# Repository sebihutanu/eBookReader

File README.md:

# OpenBook 

## Implementation Steps

### Schematic Design
I used all the required modules (ESP32-C6, BME688, RTC, Display, etc.) based on the reference schematic. I maintained consistent net naming and used components from the provided library.

### Component Placement
I followed the recommended placement, especially for the ESP32 module (antenna area), buttons, USB port, and display header. All components were placed on the TOP layer, as required.

### Manual Routing
Power traces (3V3, VBAT, VBUS, VUSB, VCC, EPD_3V3, EPD_3V3_C) were routed using a width of 0.3 mm, and signal traces were routed with 0.15 mm width.

### Ground Planes & Via Stitching
I created ground planes on both Top and Bottom layers, connected through via stitching. The area under the ESP32 antenna was excluded (no copper or vias) to ensure proper wireless performance.

### Silkscreen & Test Pads
All components were labeled using only their reference designators (R1, C1, etc.) without values. Test pads were clearly labeled in silkscreen (TX, RX, MISO, VBAT, GND, etc.).

### 3D Model & Enclosure
The final 3D model includes the PCB, display, battery (modeled based on datasheet dimensions), and the official provided enclosure. I verified the alignment of the USB port, buttons, and display header with the housing.

## Component List

- **ESP32-C6-WROOM-1-N8**: Main microcontroller. Supports Wi-Fi 6 (2.4GHz), Bluetooth 5, Thread, and Zigbee. Used for control logic and communication. 
    - **Price**: 14.70 RON
    - **Quantity**: 1
    - **Link**: https://ro.mouser.com/datasheet/2/891/Espressif_ESP32_C6_WROOM_1__Datasheet_V0_1_PRELIMI-3239987.pdf
    - **Datasheet**: https://ro.mouser.com/ProductDetail/Espressif-Systems/ESP32-C6-WROOM-1-N8?qs=8Wlm6%252BaMh8ST02Gmwp74cw%3D%3D

- **W25Q512JVEIQ**: 64MB NOR flash memory. Stores firmware, assets, or user data. Communicates via SPI.
    - **Price**: 28.91 RON
    - **Quantity**: 1
    - **Link**: https://ro.mouser.com/ProductDetail/Winbond/W25Q512JVEIQ?qs=l7cgNqFNU1jw6svr3at6tA%3D%3D
    - **Datasheet**: https://ro.mouser.com/datasheet/2/949/Winbond_W25Q512JV_Datasheet-3240039.pdf

- **MAX17048G+T10**: Fuel gauge IC. Provides battery charge level monitoring via I2C.
    - **Price**: 21.19 RON
    - **Quantity**: 1
    - **Link**: https://ro.mouser.com/ProductDetail/Analog-Devices-Maxim-Integrated/MAX17048G%2bT10?qs=D7PJwyCwLAoGnnn8jEPRBQ%3D%3D
    - **Datasheet**: https://ro.mouser.com/datasheet/2/609/MAX17048_MAX17049-3469099.pdf

- **MCP73831**: Li-Ion/Li-Poly battery charging IC. Controls charging current and status indication.
    - **Price**: 3.72 RON
    - **Quantity**: 1
    - **Link**: https://ro.mouser.com/ProductDetail/Microchip-Technology/MCP73831-2ACI-MC?qs=hH%252BOa0VZEiBneYTVdpuVdg%3D%3D
    - **Datasheet**: https://ro.mouser.com/datasheet/2/268/MCP73831_Family_Data_Sheet_DS20001984H-3441711.pdf

- **XC6220A331MR-G**: Low-dropout (LDO) voltage regulator. Converts USB input (5V) to stable 3.3V for the system.
    - **Price**: 2.50 RON
    - **Quantity**: 1
    - **Link**: https://ro.mouser.com/ProductDetail/Torex-Semiconductor/XC6220A331MR-G?qs=AsjdqWjXhJ8ZSWznL1J0gg%3D%3D
    - **Datasheet**: https://ro.mouser.com/datasheet/2/760/xc6220-3371556.pdf

- **DS3231SN#**: High-accuracy real-time clock (RTC) with battery backup. Communicates over I2C.
    - **Price**: 7.23 RON
    - **Quantity**: 1
    - **Link**: https://ro.mouser.com/ProductDetail/Maxim-Integrated/DS3231SN%23?qs=0x2j%252B5q%252B3v4%252B7g%252B6J9wXQ%3D%3D
    - **Datasheet**: https://ro.mouser.com/datasheet/2/609/DS3231-DS3231M-DS3231S

- **BME688 (ESP32_WROVER_BME688)**: Environmental sensor. Measures temperature, humidity, pressure, and gas (VOC). Uses I2C.
    - **Price**: 48.90 RON
    - **Quantity**: 1
    - **Link**: https://ro.mouser.com/ProductDetail/Bosch-Sensortec/BME688?qs=IS%252B4QmGtzzqQoVDscqwx3A%3D%3D
    - **Datasheet**: https://ro.mouser.com/datasheet/2/783/bst_bme688_fl000-2307034.pdf

- **CPH3225A**: Supercapacitor used for RTC backup power.
    - **Price**: 11.04 RON
    - **Quantity**: 1
    - **Link**: https://ro.mouser.com/ProductDetail/Seiko-Semiconductors/CPH3225A?qs=3etwrb1wR%252BhUOph6lAO7eg%3D%3D
    - **Datasheet**: https://ro.mouser.com/datasheet/2/360/Seiko_Instruments_MicroBattery_E_20230330_2024Jan_-3561061.pdf

- **744043680IND_4828-WE-TPC_WRE**: Inductor (68µH). Used for filtering or part of the power supply circuit.
    - **Price**: 6.44 RON
    - **Quantity**: 1
    - **Link**: https://ro.mouser.com/ProductDetail/Wurth-Elektronik/744043680?qs=PGXP4M47uW6VkZq%252BkzjrHA%3D%3D
    - **Datasheet**: https://www.we-online.com/components/products/datasheet/744043680.pdf

- **MBR0530**: Schottky diodes. Used for reverse voltage protection and power path steering.
    - **Price**: 0.90 RON
    - **Quantity**: 3
    - **Link**: https://ro.mouser.com/ProductDetail/onsemi/MBR0530T3G?qs=3JMERSakebpEmdUS6GetdQ%3D%3D
    - **Datasheet**: https://www.onsemi.com/PowerSolutions/product.do?id=MBR0530T3G

- **BD5229G-TR**: Voltage detector. Used for power-on reset or system supervisory functions.
    - **Price**: 3.72 RON
    - **Quantity**: 1
    - **Link**: https://ro.mouser.com/ProductDetail/ROHM-Semiconductor/BD5229G-TR?qs=4kLU8WoGk0vvnhrrYwdszw%3D%3D
    - **Datasheet**: https://fscdn.rohm.com/en/products/databook/datasheet/ic/power/voltage_detector/bd52xxg-e.pdf

- **SI1308EDL-T1-GE3**: N-channel MOSFET. Used for switching or power control.
    - **Price**: 2.07 RON
    - **Quantity**: 1
    - **Link**: https://ro.mouser.com/ProductDetail/Vishay-Semiconductors/SI1308EDL-T1-GE3?qs=bX1%252BNvsK%2FBramh9tgpOaEw%3D%3D
    - **Datasheet**: https://www.vishay.com/doc?63399

- **DMG2305UX**: P-channel MOSFET. Used in power switching or display driving.
    - **Price**: 0.95 RON
    - **Quantity**: 2
    - **Link**: https://ro.mouser.com/ProductDetail/Diodes-Incorporated/DMG2305UX-7?qs=L1DZKBg7t5F%2FNBHrjfxC%252Bg%3D%3D
    - **Datasheet**: https://www.diodes.com/assets/Datasheets/DMG2305UX.pdf

- **USBLC6-2SC6Y**: ESD protection array for USB lines.
    - **Price**: 2.16 RON
    - **Quantity**: 1
    - **Link**: https://ro.mouser.com/ProductDetail/STMicroelectronics/USBLC6-2SC6Y?qs=gNDSiZmRJS%2FOgDexvXkdow%3D%3D
    - **Datasheet**: https://ro.mouser.com/datasheet/2/389/usblc6_2sc6y-1852505.pdf

- **PGB1010603MR**: ESD suppressor / protection component for various I/O lines.
    - **Price**: 1.98 RON
    - **Quantity**: 6
    - **Link**: https://ro.mouser.com/ProductDetail/Littelfuse/PGB1010603MR?qs=gu7KAQ731URLg4GSnNNN7Q%3D%3D
    - **Datasheet**: https://www.littelfuse.com/assetdocs/pulseguard-esd-suppressors-pgb1-datasheet?assetguid=8a337998-d54d-466b-be4e-dc5bcd1f9321

- **TPTP20R**: Test pads. Used for debugging and electrical measurements (e.g. TX, RX, GND, etc.).

- **FH34SRJ-24S-0.5SH(99)**: FPC connector. Used for connecting the e-paper display.
    - **Price**: 12.87 RON
    - **Quantity**: 1
    - **Link**: https://ro.mouser.com/ProductDetail/Hirose-Connector/FH34SRJ-24S-0.5SH99?qs=vcbW%252B4%252BSTIpKBl5ap9J8Fw%3D%3D
    - **Datasheet**: https://ro.mouser.com/datasheet/2/185/FH34SRJ_24S_0_5SH_99__CL0580_1255_6_99_2DDrawing_0-1615044.pdf

- **SAMACSYS_PARTS_USB4110-GF-A**: USB Type-C connector. Used for charging and potential data communication.
    - **Price**: 5.84 RON
    - **Quantity**: 1
    - **Link**: https://ro.mouser.com/ProductDetail/GCT/USB4110-GF-A?qs=KUoIvG%2F9IlYiZvIXQjyJeA%3D%3D
    - **Datasheet**: https://ro.mouser.com/datasheet/2/837/GCT_USB4110_Product_Drawing___20k_cycles-3455479.pdf

- **112A-TAAR-R03_ATTEND3DMODEL**: MicroSD card connector (Push-Push type).
    - **Price**: 7.08 RON
    - **Quantity**: 1
    - **Link**: https://www.digikey.in/en/products/detail/attend-technology/112A-TAAR-R03/17633923
    - **Datasheet**: https://www.attend.com.tw/data/download/file/112A-TAAR-R03_Spec.pdf

- **QWIIC_CONNECTORJS-1MM**: Qwiic I2C connector. Simplifies connecting I2C peripherals.
    - **Price**: 2.30 RON
    - **Quantity**: 1
    - **Link**: https://www.sparkfun.com/qwiic-jst-connector-smd-4-pin-horizontal.html
    - **Datasheet**: https://cdn.sparkfun.com/assets/parts/1/2/2/8/9/Qwiic_Connector_Datasheet.pdf

- **BUTTON_CUSYOMV1**: Push buttons for user input. Includes RESET, BOOT, and FUNCTION buttons.

- **SJ**: Solder jumper. Used to configure hardware options or break/join signals manually.
    - **Price**: 0.55 RON
    - **Quantity**: 1
    - **Link**: https://ro.mouser.com/ProductDetail/Walsin/WR08X000-PGL?qs=1mbolxNpo8eMafhL38cnrw%3D%3D
    - **Datasheet**: https://www.farnell.com/datasheets/2813407.pdf

- **ESP32C6_VARISTORCN1812**: Varistor. Protects against voltage spikes on power lines.
    - **Price**: 2.68 RON
    - **Quantity**: 1
    - **Link**: https://ro.mouser.com/ProductDetail/Bourns/MOV-14D101K?qs=CQ3B1E%252BbPs1zZItCYuJaag%3D%3D
    - **Datasheet**: https://www.mouser.com/datasheet/2/54/MOV14D-57555.pdf?srsltid=AfmBOor_t5WSKE0HqggGW0q-lqbsQwPTZJZ8SAvWUZSrGmLf1ZZCwM8q

- **ESP32_WROVER_AVX (SD0805S020S1R0)**: Schottky diode (another variant). Also used for power line protection.
    - **Price**: 1.46 RON
    - **Quantity**: 1
    - **Link**: https://ro.mouser.com/ProductDetail/KYOCERA-AVX/SD0805S020S1R0?qs=jCA%252BPfw4LHbpkAoSnwrdjw%3D%3D
    - **Datasheet**: https://ro.mouser.com/datasheet/2/40/schottky-3165252.pdf

- **ADAFRUIT_LEDCHIP-LED0603**: Surface-mount LED (0603). Used as charge indicator or status LED.
    - **Price**: 0.50 RON
    - **Quantity**: 1
    - **Link**: https://www.niden.ro/led-uri-smd/4560-led-smd-0603-alb-rece.html
    - **Datasheet**: https://www.mouser.com/datasheet/2/423/LSM0603472V_(1)-1379786.pdf?srsltid=AfmBOoqr62HLQ-IfSohXT73tjl0UQHGyLpv_UpJG0VLORMsRNFTPFgMo

- **EAGLE-LTSPICE_CC0402 / RR0402 / RCL_CPOL-EUCT3528**: Capacitors and resistors in SMD packages. Used for decoupling, filtering, and biasing.
    - **Price**: 0.10 RON
    - **Quantity**: 1
    - **Link**: https://www.digikey.com/en/products/detail/rohm-semiconductor/CC0402/1000000
    - **Datasheet**: https://www.rohm.com/datasheet/CC0402

- **CC0402**: Capacitor (0402 package). Used for decoupling and filtering.
    - **Price**: 0.52 RON
    - **Quantity**: 24
    - **Link**: https://ro.mouser.com/ProductDetail/TAIYO-YUDEN/MCASU105SCG100JFNA01?qs=HFfMDpzxxd3IzDXquDJtfA%3D%3D
    - **Datasheet**: https://ro.mouser.com/datasheet/2/396/TAIYO_YUDEN_04_29_2024_MCASU105SCG100JFNA01_SS-3451431.pdf

- **RR0402**: Resistor (0402 package). Used for pull-up/pull-down or biasing.
    - **Price**: 0.27 RON
    - **Quantity**: 24
    - **Link**: https://ro.mouser.com/ProductDetail/Vishay-Dale/CRCW04020000Z0EEHP?qs=Imq1NPwxi74NTc567q7flQ%3D%3D
    - **Datasheet**: https://www.vishay.com/doc?20043

- **RCL_CPOL-EUCT3528**: Capacitor (EUCT3528 package). Used for decoupling and filtering.
    - **Price**: 6.50 RON
    - **Quantity**: 1
    - **Link**: https://ro.mouser.com/ProductDetail/Vishay-Sprague/TX3B336K016C1000?qs=HFfMDpzxxd327XT3TleiYg%3D%3D
    - **Datasheet**: https://www.vishay.com/doc?40283

- **Battery**: 3.7V Li-Ion battery (not included in the schematic). Used for powering the device when not connected to USB.
    - **Price**: 29.50 RON
    - **Quantity**: 1
    - **Link**: https://www.tme.eu/Document/e0683d8c34e6d878124489f71bffb6ee/cel0014.pdf
    - **Datasheet**: https://www.tme.eu/Document/e0683d8c34e6d878124489f71bffb6ee/cel0014.pdf

- **Display**: E-paper display (not included in the schematic). Used for displaying information to the user.
    - **Price**: 258.85 RON
    - **Quantity**: 1
    - **Link**: https://www.waveshare.com/7.5inch-e-paper-hat.htm
    - **Datasheet**: https://files.waveshare.com/upload/6/60/7.5inch_e-Paper_V2_Specification.pdf
    
> **Total Cost**: 485.50 RON (approx. 100 EUR)

> **Note:** All standard resistors and capacitors are SMD 0402 unless otherwise specified. Decoupling capacitors (100nF) are placed close to IC power pins for stability.

## Block Diagram

## ESP32-C6 Pin Utilization

| ESP32-C6 Pin | Signal Name   | Connected Component         | Description / Purpose                                           |
|--------------|---------------|-----------------------------|-----------------------------------------------------------------|
| EN           | RESET         | -                           | Reset input, active HIGH; used to restart the microcontroller   |
| GPIO0        | INT_RTC       | RTC (DS3231)                | External interrupt input from RTC alarm                         |
| GPIO1        | 32KHZ         | RTC (DS3231)                | 32 kHz reference clock from RTC                                 |
| GPIO2        | MISO          | SD card / Flash             | SPI MISO line for data input                                    |
| GPIO3        | EPD_BUSY      | E-paper display             | Busy status from EPD module                                     |
| GPIO4        | SS_SD         | SD card                     | Chip select for SD card on SPI                                  |
| GPIO5        | EPD_DC        | E-paper display             | Data/command control signal for EPD                             |
| GPIO6        | SCK           | SPI bus                     | Serial clock for SPI communication                              |
| GPIO7        | MOSI          | SPI bus                     | SPI data output                                                 |
| GPIO8        | GPIO8         | -                           | Unused general-purpose pin (test/debug)                         |
| GPIO9        | IO/BOOT       | Push-button                 | Used to enter bootloader mode for programming                   |
| GPIO10       | EPD_CS        | E-paper display             | Chip select for EPD module                                      |
| GPIO11       | FLASH_CS      | External flash (W25Q512)    | Chip select for SPI flash memory                                |
| GPIO12       | USB_D-        | USB-C connector             | USB differential data line (negative)                           |
| GPIO13       | USB_D+        | USB-C connector             | USB differential data line (positive)                           |
| GPIO15       | IO/CHANGE     | Push-button                 | General-purpose button input                                    |
| GPIO16 (TXD) | TX            | UART                        | Serial transmission line                                        |
| GPIO17 (RXD) | RX            | UART                        | Serial reception line                                           |
| GPIO18       | RTC_RST       | RTC (DS3231)                | Reset control for RTC                                           |
| GPIO19       | I2C_RST       | I2C devices                 | I2C reset or control signal                                     |
| GPIO20       | EPD_3V3_C     | E-paper display             | Power control or monitoring line for EPD                        |
| GPIO21       | SDA           | I2C devices (BME688, Fuel Gauge) | I2C data line for sensors and peripherals                  |
| GPIO22       | SCL           | I2C devices (BME688, Fuel Gauge) | I2C clock line for sensors and peripherals                 |
| GPIO23       | EPD_RST       | E-paper display             | Reset signal for the EPD display                                |

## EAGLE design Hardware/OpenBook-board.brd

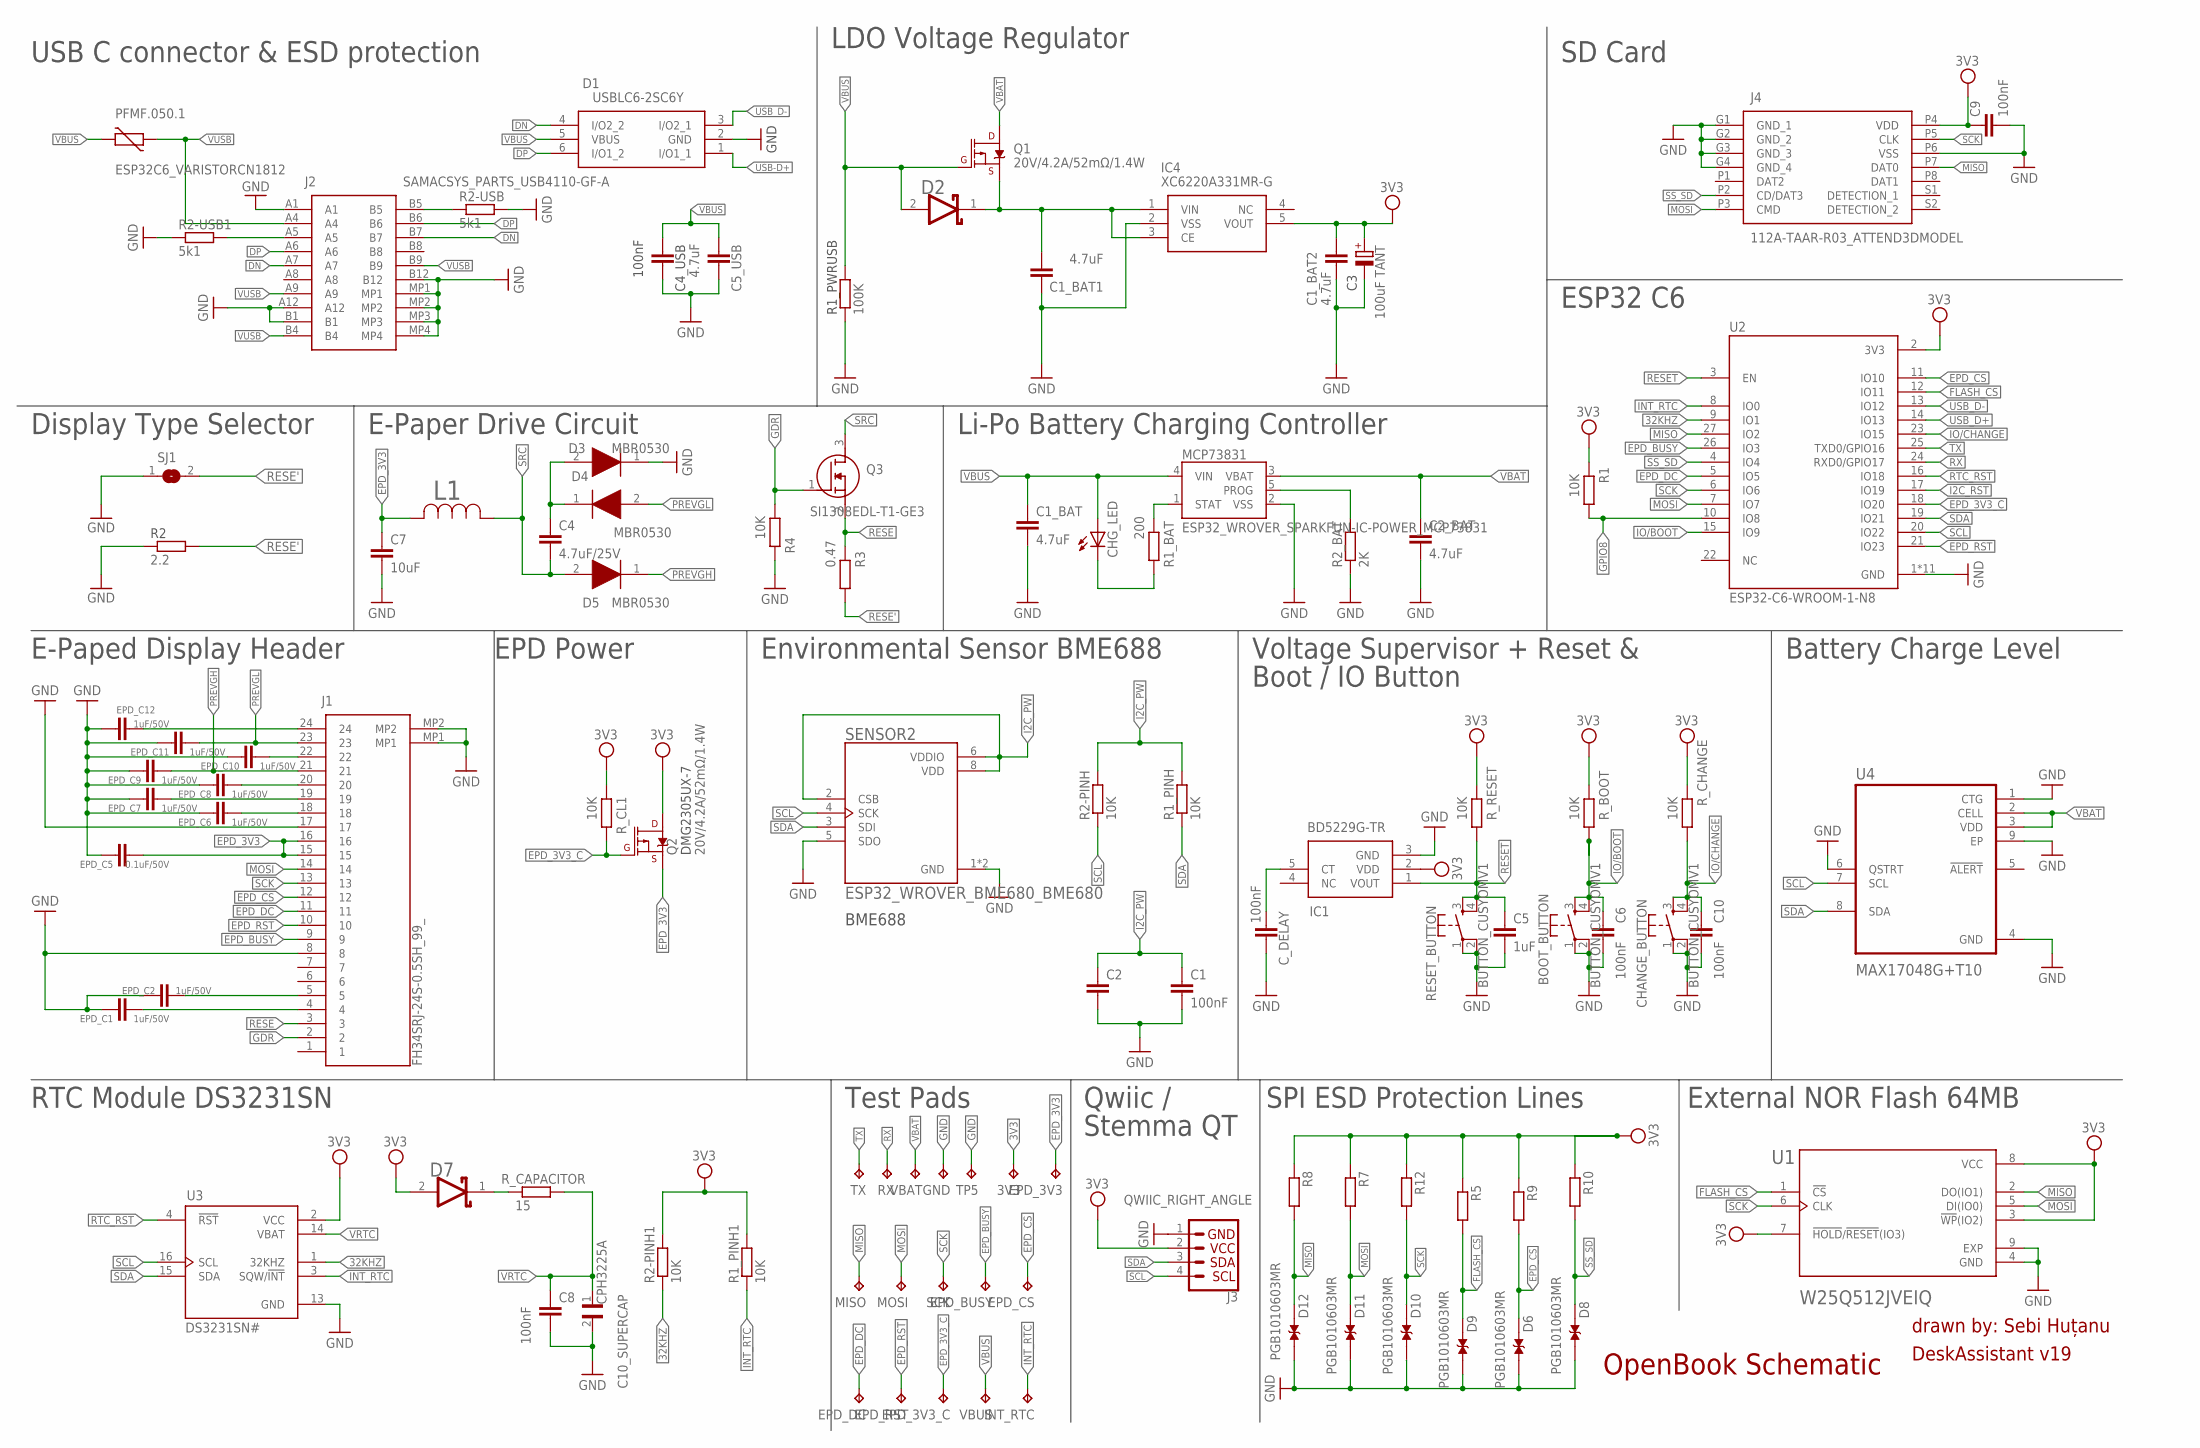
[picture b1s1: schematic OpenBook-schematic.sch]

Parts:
3V3: TPTP20R; TP20R
BOOT_BUTTON: BUTTON_CUSYOMV1; MYBUTTON
C1, C4_USB, C6, C8, C10: 100nF; EAGLE-LTSPICE_C0402
C1_BAT, C1_BAT1, C2_BAT, C5_USB: 4.7uF; EAGLE-LTSPICE_C0402
C1_BAT2: 4.7uF; ESP32_WROVER_EAGLE-LTSPICE_C0402
C2: EAGLE-LTSPICE_CC0402; EAGLE-LTSPICE_C0402
C3: 100uF TANT; RCL_CT3528
C4: 4.7uF/25V; EAGLE-LTSPICE_C0402
C5: 1uF; EAGLE-LTSPICE_C0402
C7: 10uF; ESP32_WROVER_EAGLE-LTSPICE_C0402
C9: 100nF; ESP32_WROVER_EAGLE-LTSPICE_C0402
C10_SUPERCAP: CPH3225A; CAPCP3225X100N
CHANGE_BUTTON: BUTTON_CUSYOMV1; MYBUTTON
CHG_LED: ADAFRUIT_LEDCHIP-LED0603; ADAFRUIT_CHIP-LED0603
C_DELAY: 100nF; EAGLE-LTSPICE_C0402
D1: USBLC6-2SC6Y; SOT95P280X145-6N
D2, D7: ESP32_WROVER_AVX---SD0805S020S1R0_AVX_SD0805S020S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; ESP32_WROVER_AVX---SD0805S020S1R0_AVX_SD0805S020S1R0_0
D3, D4, D5: MBR0530; SOD3716X135N
D6, D8, D9, D10, D11, D12: PGB1010603MR; DIOC1608X36N
EPD_3V3, EPD_3V3_C: TPTP20R; TP20R
EPD_BUSY: TPTP20R; TP20R
EPD_C1, EPD_C2, EPD_C6, EPD_C7, EPD_C8, EPD_C9, EPD_C10, EPD_C11, EPD_C12: 1uF/50V; EAGLE-LTSPICE_C0402
EPD_C5: 0.1uF/50V; EAGLE-LTSPICE_C0402
EPD_CS: TPTP20R; TP20R
EPD_DC: TPTP20R; TP20R
EPD_RST: TPTP20R; TP20R
GND: TPTP20R; TP20R
IC1: BD5229G-TR; SOT95P280X125-5N
IC4: XC6220A331MR-G; SOT95P280X120-5N
INT_RTC: TPTP20R; TP20R
J1: FH34SRJ-24S-0.5SH_99_; FH34SRJ24S05SH99
J2: SAMACSYS_PARTS_USB4110-GF-A; SAMACSYS_PARTS_USB4110GFA
J3: QWIIC_RIGHT_ANGLE; JST04_1MM_RA
J4: 112A-TAAR-R03_ATTEND3DMODEL; 112ATAARR03ATTEND
L1: 744043680IND_4828-WE-TPC_WRE; IND_4828-WE-TPC_WRE
MCP73831: ESP32_WROVER_SPARKFUN-IC-POWER_MCP73831; ESP32_WROVER_SPARKFUN-IC-POWER_SOT23-5
MISO: TPTP20R; TP20R
MOSI: TPTP20R; TP20R
PFMF.050.1: ESP32C6_VARISTORCN1812; ESP32C6_VARISTOR_CT/CN1812
Q1, Q2: 20V/4.2A/52mΩ/1.4W; ESP32_WROVER_SPARKFUN-DISCRETESEMI_SOT23-3
Q3: SI1308EDL-T1-GE3; SOT65P210X110-3N
R1, R1_PINH, R1_PINH1, R2-PINH, R2-PINH1, R4: 10K; ESP32_WROVER_EAGLE-LTSPICE_R0402
R1_BAT: 200; ESP32_WROVER_EAGLE-LTSPICE_R0402
R1_PWRUSB: 100K; ESP32_WROVER_EAGLE-LTSPICE_R0402
R2: 2.2; ESP32_WROVER_EAGLE-LTSPICE_R0402
R2-USB, R2-USB1: 5k1; ESP32_WROVER_EAGLE-LTSPICE_R0402
R2_BAT: 2K; ESP32_WROVER_EAGLE-LTSPICE_R0402
R3: 0.47; ESP32_WROVER_EAGLE-LTSPICE_R0402
R5, R7, R8, R9, R10, R12: ESP32_WROVER_EAGLE-LTSPICE_RR0402; ESP32_WROVER_EAGLE-LTSPICE_R0402
RESET_BUTTON: BUTTON_CUSYOMV1; MYBUTTON
RX: TPTP20R; TP20R
R_BOOT: 10K; ESP32_WROVER_EAGLE-LTSPICE_R0402
R_CAPACITOR: 15; ESP32_WROVER_EAGLE-LTSPICE_R0402
R_CHANGE: 10K; ESP32_WROVER_EAGLE-LTSPICE_R0402
R_CL1: 10K; ESP32_WROVER_EAGLE-LTSPICE_R0402
R_RESET: 10K; ESP32_WROVER_EAGLE-LTSPICE_R0402
SCK: TPTP20R; TP20R
SENSOR2: ESP32_WROVER_BME680_BME680; ESP32_WROVER_BME680_PSON80P300X300X100-8N
SJ1: SJ
TP5: TPTP20R; TP20R
TX: TPTP20R; TP20R
U1: W25Q512JVEIQ; SON127P600X800X80-9N
U2: ESP32-C6-WROOM-1-N8; XCVR_ESP32-C6-WROOM-1-N8
U3: DS3231SN#; SOIC127P1032X265-16N
U4: MAX17048G+T10; SON50P200X200X80-9N
VBAT: TPTP20R; TP20R
VBUS: TPTP20R; TP20R

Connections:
3V3: 3V3.TP, C1_BAT2.1, C3.+, C9.1, D7.2 (ANODE), IC1.2 (VDD), IC4.5 (VOUT), J4.P4 (VDD), Q2.3 (D), R1.2, R1_PINH1.2, R2-PINH1.2, R5.1, R7.1, R8.1, R9.1, R10.1, R12.1, R_BOOT.2, R_CHANGE.2, R_CL1.2, R_RESET.2, U1.3 (!WP!(IO2)), U1.7 (!HOLD!/!RESET!(IO3)), U1.8 (VCC), U2.2 (3V3), U3.2 (VCC)
32KHZ: R2-PINH1.1, U2.9 (IO1), U3.1 (32KHZ)
DN: D1.4 (I/O2_2), J2.A7, J2.B7
DP: D1.6 (I/O1_2), J2.A6, J2.B6
EPD_3V3: C7.1, EPD_3V3.TP, EPD_C5.2, J1.15, J1.16, L1.2, Q2.2 (S)
EPD_3V3_C: EPD_3V3_C.TP, Q2.1 (G), R_CL1.1, U2.18 (IO20)
EPD_BUSY: EPD_BUSY.TP, J1.9, U2.26 (IO3)
EPD_CS: D6.2, EPD_CS.TP, J1.12, R9.2, U2.11 (IO10)
EPD_DC: EPD_DC.TP, J1.11, U2.5 (IO5)
EPD_RST: EPD_RST.TP, J1.10, U2.21 (IO23)
FLASH_CS: D9.2, R5.2, U1.1 (!CS), U2.12 (IO11)
GDR: J1.2, Q3.1 (G), R4.2
GND: BOOT_BUTTON.1, BOOT_BUTTON.2, C1.2, C1_BAT.2, C1_BAT1.1, C1_BAT2.2, C2.2, C2_BAT.2, C3.-, C4_USB.2, C5.2, C5_USB.2, C6.2, C7.2, C8.2, C9.2, C10.2, C10_SUPERCAP.2, CHANGE_BUTTON.1, CHANGE_BUTTON.2, C_DELAY.2, D1.2 (GND), D3.1 (K), D6.1, D8.1, D9.1, D10.1, D11.1, D12.1, EPD_C1.1, EPD_C2.1, GND.TP, IC1.3 (GND), IC4.2 (VSS), J1.8, J1.17, J1.MP1, J1.MP2, J2.A1, J2.A12, J2.B1, J2.B12, J2.MP1, J2.MP2, J2.MP3, J2.MP4, J3.1, J4.G1 (GND_1), J4.G2 (GND_2), J4.G3 (GND_3), J4.G4 (GND_4), J4.P6 (VSS), MCP73831.2 (VSS), R1_PWRUSB.1, R2.1, R2-USB.2, R2-USB1.1, R2_BAT.1, R4.1, RESET_BUTTON.1, RESET_BUTTON.2, SENSOR2.1 (GND), SENSOR2.5 (SDO), SENSOR2.7 (GND), SJ1.1, TP5.TP, U1.4 (GND), U1.9 (EXP), U2.1 (GND), U2.28 (GND), U2.29_1 (GND), U2.29_2 (GND), U2.29_3 (GND), U2.29_4 (GND), U2.29_5 (GND), U2.29_6 (GND), U2.29_7 (GND), U2.29_8 (GND), U2.29_9 (GND), U3.13 (GND), U4.1 (CTG), U4.4 (GND), U4.6 (QSTRT), U4.9 (EP)
GPIO8: R1.1, U2.10 (IO8)
I2C_PW: C1.1, C2.1, R1_PINH.2, R2-PINH.2, SENSOR2.2 (CSB), SENSOR2.6 (VDDIO), SENSOR2.8 (VDD)
I2C_RST: U2.17 (IO19)
INT_RTC: INT_RTC.TP, R1_PINH1.1, U2.8 (IO0), U3.3 (SQW/!INT)
IO/BOOT: BOOT_BUTTON.3, BOOT_BUTTON.4, C6.1, R_BOOT.1, U2.15 (IO9)
IO/CHANGE: C10.1, CHANGE_BUTTON.3, CHANGE_BUTTON.4, R_CHANGE.1, U2.23 (IO15)
MISO: D12.2, J4.P7 (DAT0), MISO.TP, R8.2, U1.2 (DO(IO1)), U2.27 (IO2)
MOSI: D11.2, J1.14, J4.P3 (CMD), MOSI.TP, R7.2, U1.5 (DI(IO0)), U2.7 (IO7)
unnamed: C_DELAY.1, IC1.5 (CT)
unnamed: C1_BAT1.2, D2.1 (CATHODE), IC4.1 (VIN), IC4.3 (CE), Q1.2 (S)
unnamed: MCP73831.1 (STAT), R1_BAT.2
unnamed: J2.B5, R2-USB.1
unnamed: J2.A5, R2-USB1.2
unnamed: C4.1, D3.2 (A), D4.1 (K)
unnamed: CHG_LED.C, R1_BAT.1
unnamed: MCP73831.5 (PROG), R2_BAT.2
unnamed: EPD_C12.2, J1.24
unnamed: EPD_C10.2, J1.22
unnamed: EPD_C8.2, J1.20
unnamed: EPD_C7.2, J1.19
unnamed: EPD_C6.2, J1.18
unnamed: D7.1 (CATHODE), R_CAPACITOR.1
unnamed: EPD_C2.2, J1.5
unnamed: EPD_C1.2, J1.4
unnamed: EPD_C5.1, EPD_C6.1, EPD_C7.1, EPD_C8.1, EPD_C9.1, EPD_C10.1, EPD_C11.1, EPD_C12.1
PREVGH: D5.1 (K), EPD_C9.2, J1.21
PREVGL: D4.2 (A), EPD_C11.2, J1.23
RESE: J1.3, Q3.2 (S), R3.2
RESE': R2.2, R3.1, SJ1.2
RESET: C5.1, IC1.1 (VOUT), RESET_BUTTON.3, RESET_BUTTON.4, R_RESET.1, U2.3 (EN)
RTC_RST: U2.16 (IO18), U3.4 (!RST)
RX: RX.TP, U2.24 (RXD0/GPIO17)
SCK: D10.2, J1.13, J4.P5 (CLK), R12.2, SCK.TP, U1.6 (CLK), U2.6 (IO6)
SCL: J3.4, R2-PINH.1, SENSOR2.4 (SCK), U2.20 (IO22), U3.16 (SCL), U4.7 (SCL)
SDA: J3.2, R1_PINH.1, SENSOR2.3 (SDI), U2.19 (IO21), U3.15 (SDA), U4.8 (SDA)
SRC: C4.2, D5.2 (A), L1.1, Q3.3 (D)
SS_SD: D8.2, J4.P2 (CD/DAT3), R10.2, U2.4 (IO4)
TX: TX.TP, U2.25 (TXD0/GPIO16)
USB-D+: D1.1 (I/O1_1)
USB_D+: U2.14 (IO13)
USB_D-: D1.3 (I/O2_1), U2.13 (IO12)
VBAT: C2_BAT.1, MCP73831.3 (VBAT), Q1.3 (D), U4.2 (CELL), U4.3 (VDD), VBAT.TP
VBUS: C1_BAT.1, C4_USB.1, C5_USB.1, CHG_LED.A, D1.5 (VBUS), D2.2 (ANODE), MCP73831.4 (VIN), PFMF.050.1.2, Q1.1 (G), R1_PWRUSB.2, VBUS.TP
VRTC: C8.1, C10_SUPERCAP.1, R_CAPACITOR.2, U3.14 (VBAT)
VUSB: J2.A4, J2.A9, J2.B4, J2.B9, PFMF.050.1.1

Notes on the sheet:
USB C connector & ESD protection
LDO Voltage Regulator
SD Card
OpenBook Schematic
drawn by: Sebi Huțanu
DeskAssistant v19
Display Type Selector
E-Paper Drive Circuit
Li-Po Battery Charging Controller
ESP32 C6
E-Paped Display Header
DMG2305UX-7
EPD Power
Environmental Sensor BME688
BME688
Voltage Supervisor + Reset &
Boot / IO Button
Battery Charge Level
RTC Module DS3231SN
Test Pads
Qwiic /
Stemma QT
SPI ESD Protection Lines
External NOR Flash 64MB

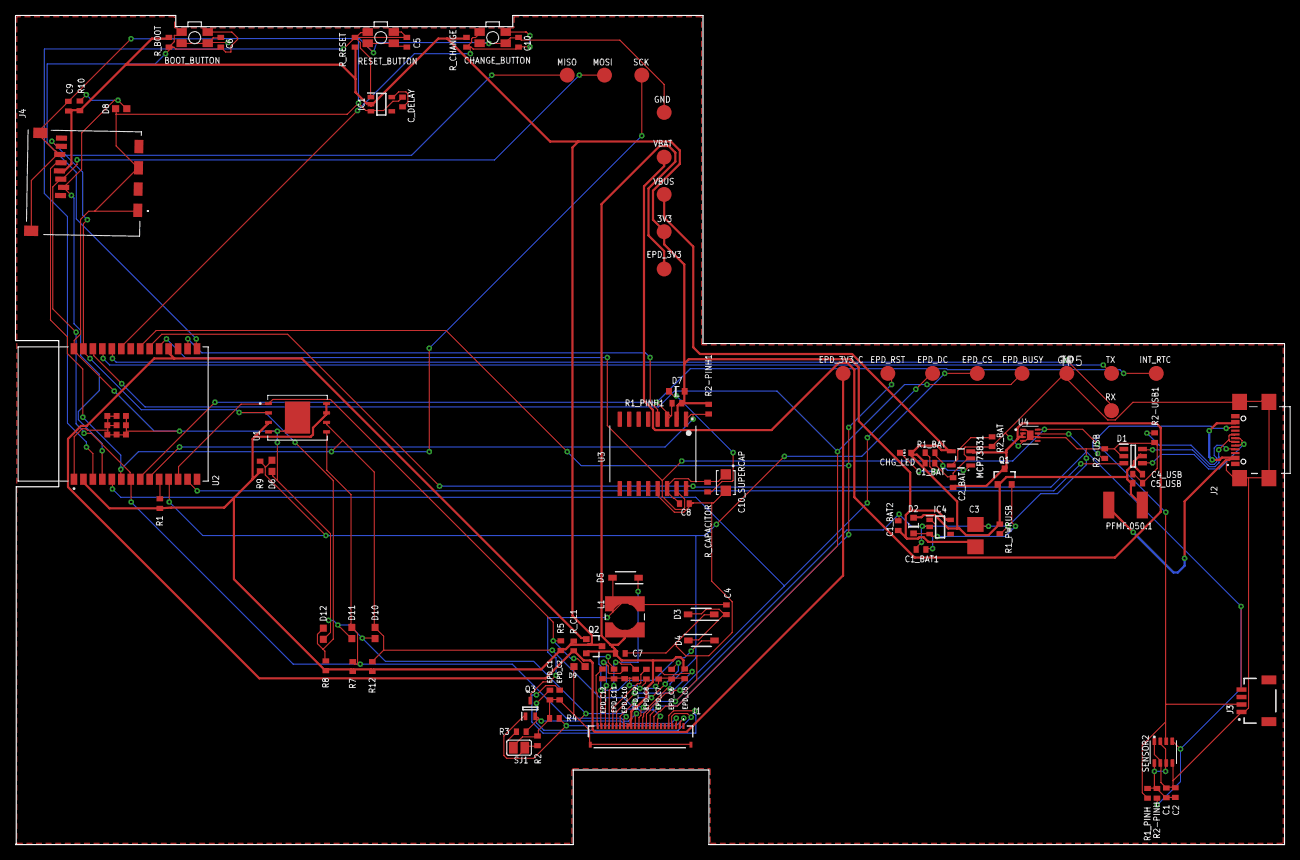
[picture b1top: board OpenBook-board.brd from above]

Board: 2 copper layers, 170.2 x 111.2 mm, 103 parts (0 on the bottom side), 55 nets.

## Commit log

2025-04-06 OpenBook
2025-04-06 Create LICENSE
2025-04-14 solved ESP32 issue
2025-04-14 solved battery issue
2025-04-14 solved missing components issue
2025-04-14 updated images

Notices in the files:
parts and their libraries:
COPYRIGHT: Copyright (C) 2024 Ultra Librarian. All rights reserved.
